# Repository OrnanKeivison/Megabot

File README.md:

# Megabot
Este repositório é dedicado ao projeto "Megabot", um software para um robô desenvolvido para a Olimpíada Brasileira de Robótica (OBR) utilizando a plataforma Arduino.

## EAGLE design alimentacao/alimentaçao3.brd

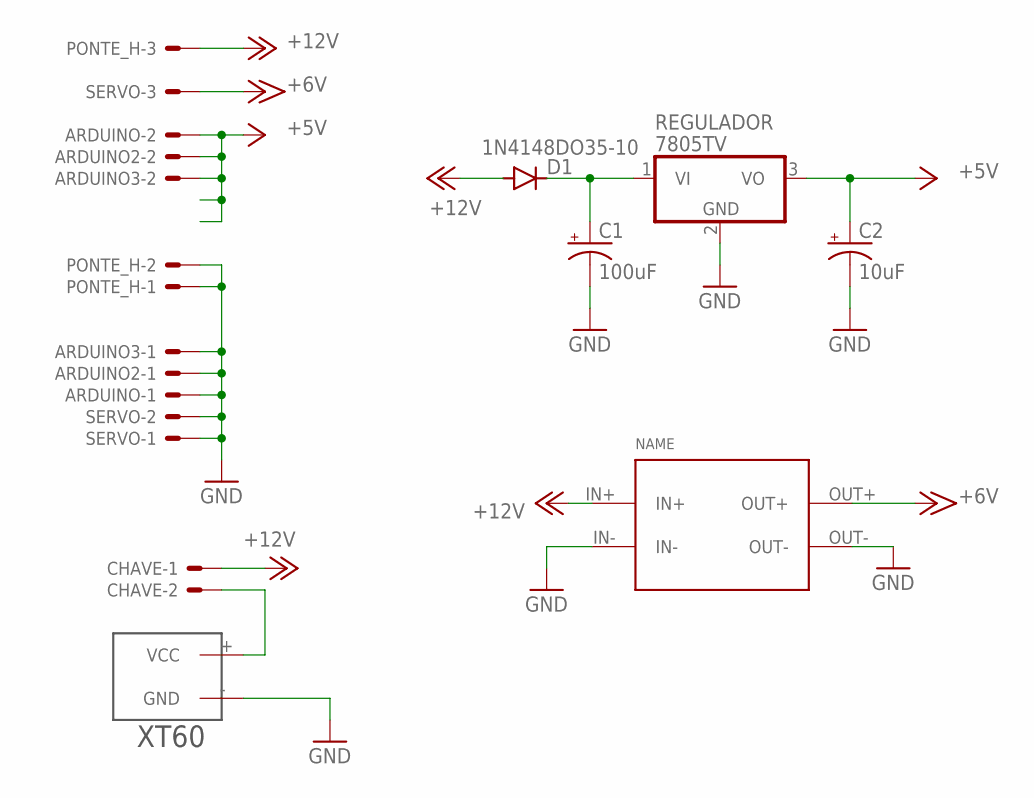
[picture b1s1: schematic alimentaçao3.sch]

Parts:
ARDUINO, ARDUINO2, ARDUINO3: KK-156-2
BUCK: CP8-ADJ
C1: 100uF; E5-4
C2: 10uF; E5-4
CHAVE: KK-156-2
D1: 1N4148DO35-10; DO35-10
PONTE_H: KK-156-3
REGULADOR: 7805TV; TO220V
SERVO: KK-156-3
U$1: XT60

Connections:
+5V: ARDUINO.2, ARDUINO2.2, ARDUINO3.2, C2.+, REGULADOR.3 (VO)
+6V: BUCK.OUT+, SERVO.3
+12V: BUCK.IN+, CHAVE.1, D1.A, PONTE_H.3
GND: ARDUINO.1, ARDUINO2.1, ARDUINO3.1, BUCK.IN-, BUCK.OUT-, C1.-, C2.-, PONTE_H.1, PONTE_H.2, REGULADOR.2 (GND), SERVO.1, SERVO.2, U$1.- (GND)
unnamed: CHAVE.2, U$1.+ (VCC)
unnamed: C1.+, D1.C, REGULADOR.1 (VI)

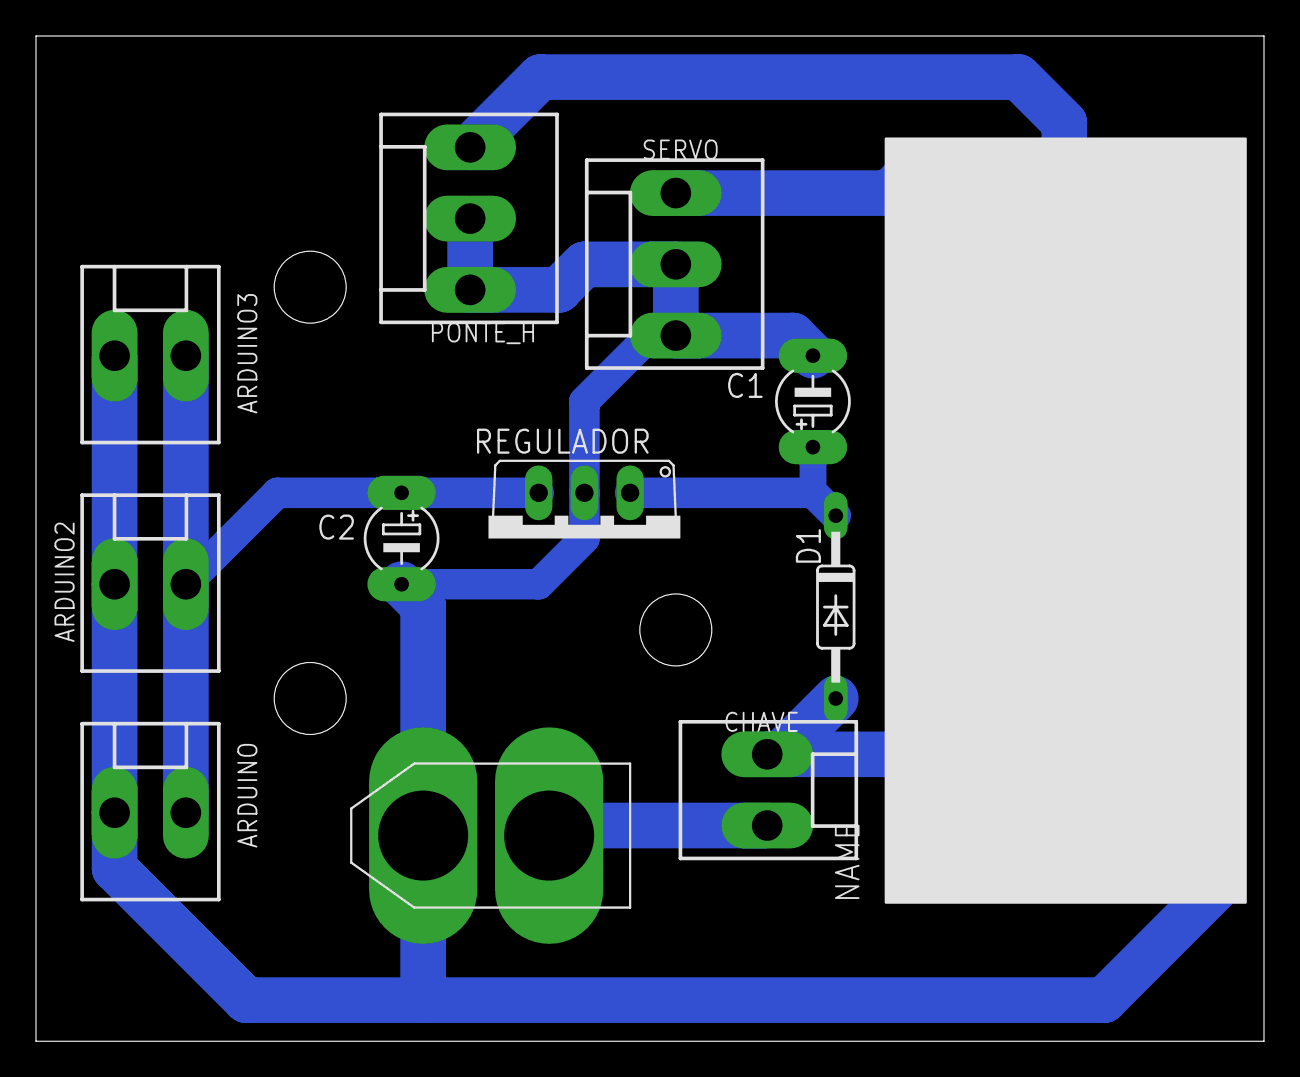
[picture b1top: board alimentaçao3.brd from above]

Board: 2 copper layers, 68.2 x 55.9 mm, 12 parts (0 on the bottom side), 6 nets.

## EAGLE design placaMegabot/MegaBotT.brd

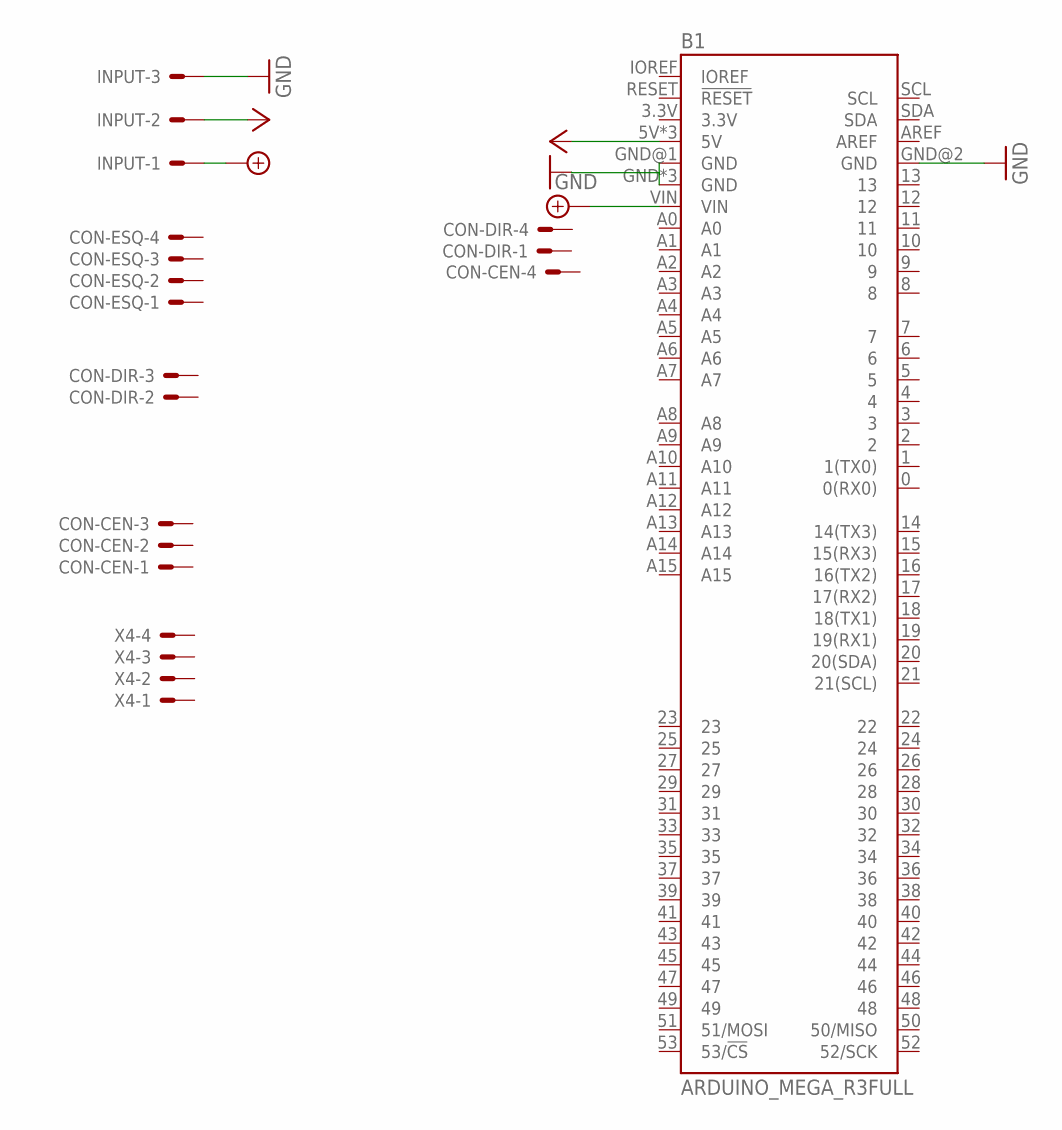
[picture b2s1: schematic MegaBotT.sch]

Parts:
B1: ARDUINO_MEGA_R3FULL; ARDUINO_MEGA_NO_SILK
CON-CEN: JST-XH-04-PIN-LONG-PAD; JST-XH-04-PACKAGE-LONG-PAD
CON-DIR: JST-XH-04-PIN-LONG-PAD; JST-XH-04-PACKAGE-LONG-PAD
CON-ESQ: JST-XH-04-PIN-LONG-PAD; JST-XH-04-PACKAGE-LONG-PAD
INPUT: KK-156-3
X4: JST-XH-04-PIN-LONG-PAD; JST-XH-04-PACKAGE-LONG-PAD

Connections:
+8V: B1.VIN, INPUT.1
GND: B1.GND, B1.GND@1 (GND), B1.GND@2 (GND), B1.GND@3 (GND), B1.GND@4 (GND), INPUT.3
VCC: B1.5V, B1.5V@1 (5V), B1.5V@2 (5V), INPUT.2

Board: 2 copper layers, 6 parts (0 on the bottom side), 3 nets, no tracks yet.

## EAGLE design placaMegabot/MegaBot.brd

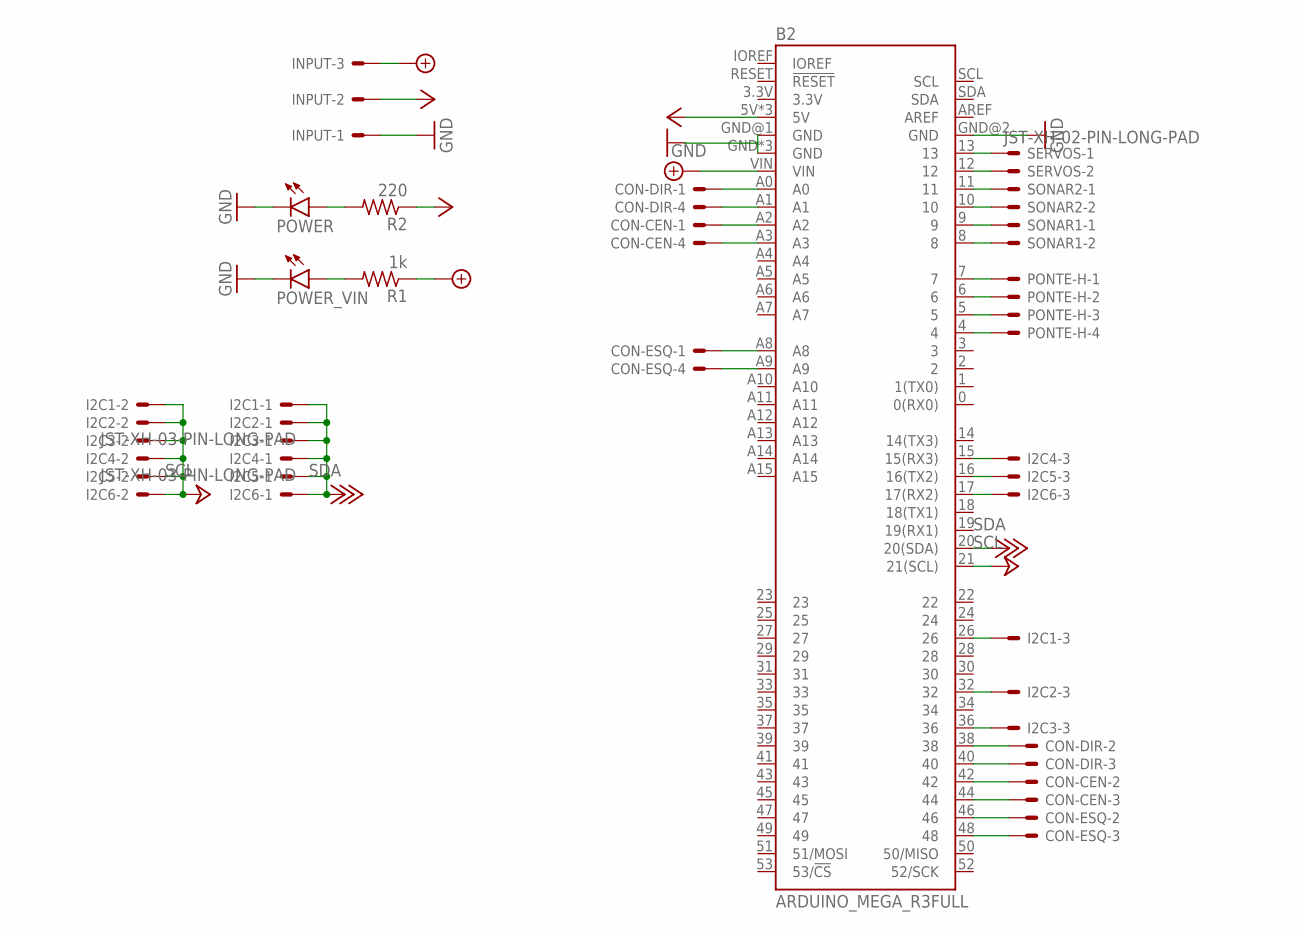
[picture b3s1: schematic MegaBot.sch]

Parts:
B2: ARDUINO_MEGA_R3FULL; ARDUINO_MEGA_NO_SILK
CON-CEN: JST-XH-04-PIN-LONG-PAD; JST-XH-04-PACKAGE-LONG-PAD
CON-DIR: JST-XH-04-PIN-LONG-PAD; JST-XH-04-PACKAGE-LONG-PAD
CON-ESQ: JST-XH-04-PIN-LONG-PAD; JST-XH-04-PACKAGE-LONG-PAD
I2C1, I2C2, I2C3, I2C4, I2C5, I2C6: JST-XH-03-PIN-LONG-PAD; JST-XH-03-PACKAGE-LONG-PAD
INPUT: KK-156-3
PONTE-H: JST-XH-04-PIN-LONG-PAD; JST-XH-04-PACKAGE-LONG-PAD
POWER: LEDLED5MM_LONG_PAD; LED5MM_LONG_PAD
POWER_VIN: LEDLED5MM_LONG_PAD; LED5MM_LONG_PAD
R1: 1k; 0204/7
R2: 220; 0204/7
SERVOS: JST-XH-02-PIN-LONG-PAD; JST-XH-02-PACKAGE-LONG-PAD
SONAR1, SONAR2: JST-XH-02-PIN-LONG-PAD; JST-XH-02-PACKAGE-LONG-PAD

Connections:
+8V: B2.VIN, INPUT.3, R1.1
+18V: B2.20 (20(SDA)), I2C1.1, I2C2.1, I2C3.1, I2C4.1, I2C5.1, I2C6.1
+24V: B2.21 (21(SCL)), I2C1.2, I2C2.2, I2C3.2, I2C4.2, I2C5.2, I2C6.2
GND: B2.GND, B2.GND@1 (GND), B2.GND@2 (GND), B2.GND@3 (GND), B2.GND@4 (GND), INPUT.1, POWER.K (C), POWER_VIN.K (C)
unnamed: B2.7, PONTE-H.1
unnamed: B2.6, PONTE-H.2
unnamed: B2.5, PONTE-H.3
unnamed: B2.4, PONTE-H.4
unnamed: B2.38, CON-DIR.2
unnamed: B2.40, CON-DIR.3
unnamed: B2.42, CON-CEN.2
unnamed: B2.44, CON-CEN.3
unnamed: B2.46, CON-ESQ.2
unnamed: B2.48, CON-ESQ.3
unnamed: B2.A0, CON-DIR.1
unnamed: B2.A1, CON-DIR.4
unnamed: B2.A2, CON-CEN.1
unnamed: B2.A3, CON-CEN.4
unnamed: B2.A8, CON-ESQ.1
unnamed: B2.A9, CON-ESQ.4
unnamed: B2.11, SONAR2.1
unnamed: B2.10, SONAR2.2
unnamed: B2.9, SONAR1.1
unnamed: B2.8, SONAR1.2
unnamed: B2.26, I2C1.3
unnamed: B2.32, I2C2.3
unnamed: B2.36, I2C3.3
unnamed: B2.15 (15(RX3)), I2C4.3
unnamed: B2.16 (16(TX2)), I2C5.3
unnamed: B2.17 (17(RX2)), I2C6.3
unnamed: B2.13, SERVOS.1
unnamed: B2.12, SERVOS.2
unnamed: POWER_VIN.A, R1.2
unnamed: POWER.A, R2.2
VCC: B2.5V, B2.5V@1 (5V), B2.5V@2 (5V), INPUT.2, R2.1

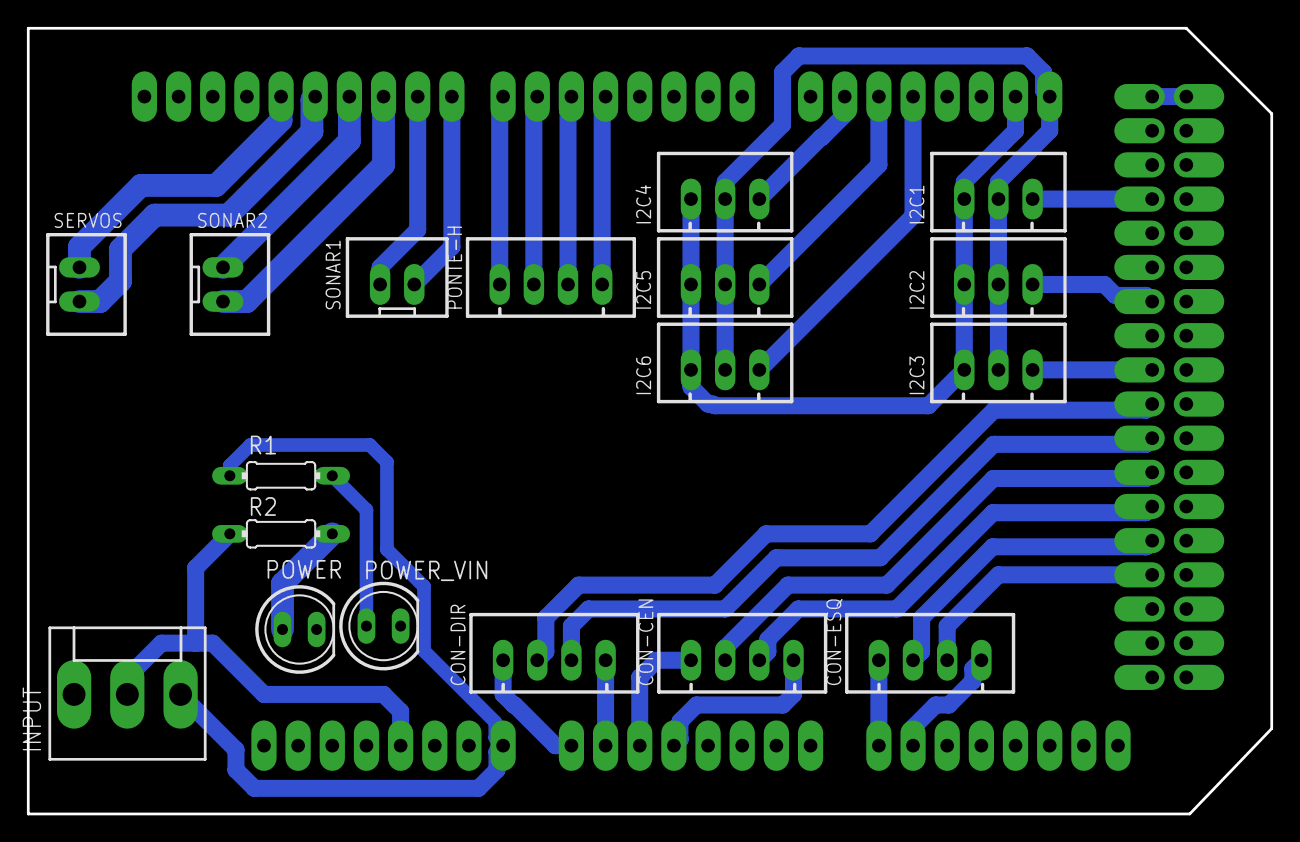
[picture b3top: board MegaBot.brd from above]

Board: 2 copper layers, 92.5 x 58.4 mm, 19 parts (0 on the bottom side), 35 nets.

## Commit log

2023-12-18 git add
2024-03-21 Adicionando arquivos iniciais
2024-03-21 Criação da classe Leds
    foi criado uma classe responsável pelo controle dos Leds.
2024-03-21 Criação da classe Strategy
    criação da classe responsável pelo controle das estrategias do robô
2024-03-21 Criação da estrategia para teste dos Leds
2024-03-21 Criação da classe Movement
    criação da classe responsável pela movimentação do robô
2024-03-21 Criação da estrategia para testar a movimentação do robô
2024-03-21 Criação da classe Reflectance
    criação da classe responsável pelos sensores de refletância do robô
2024-03-21 Criação da estrategia para testar Sensores de refletância
2024-03-21 Criação da estrategia para seguir linha
2024-03-26 Criação da classe ColorSensor
    criação da classe responsável pelos sensores de cor do robô
2024-03-26 Criação da estrategia para testar os sensores de cor
2024-03-26 Criação da estrategia para ver alguns casos de verde
2024-03-27 Criação da classe Distance
    criação da classe responsável pelos sensores de distancia do robô
2024-03-27 criação da estrategia para iniciar o robô e testar os sensores de distância

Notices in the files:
parts and their libraries:
SparkFun-Boards: Licensing: Creative Commons ShareAlike 4.0 International - https://creativecommons.org/licenses/by-sa/4.0
